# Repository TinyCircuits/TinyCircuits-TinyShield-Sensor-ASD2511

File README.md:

# TinyCircuits TinyShield Sensor Board
# ASD2511 Rev5

The design files are located in the design_files/ folder for the TinyCircuits ASD2511 Rev 5 PCB.  This is a TinyShield board (Square Version, 20mm x 20mm) that has multiple sensor ICs on it and can be built under different configurations based on the sensor needs.  This board includes a 3-axis accelerometer, 3-axis gyroscope, 3-axis compass, 9-axis IMU, barometric pressure, temperature / humidity sensor, & ambient light sensor.  

Format is in Cadsoft Eagle format - Eagle version 6.2 was used for the original design.

For more infomation on this, check out the product pages for sensors at TinyCircuits.com: https://tinycircuits.com/collections/sensors/products/combo-sensor-tinyshield

#License:

Design by TinyCircuits.
All design files are released under the Creative Commons Attribution Share-Alike 3.0 License, see the following link for details: http://creativecommons.org/licenses/by-sa/3.0

All text above must be included in any redistribution or derived design

This project uses designs and concepts developed as part of the Arduino project and the LilyPad project.  The TinyCircuits design files themselves (schematics, PCB and libraries) are not directly derived from these works' design files and have been created new, however the concepts and basic architecture behind the TinyDuino and TinyLily products are derived and we thank the hard work of the organizations below for their contributions to open-source hardware:
  
Original Arduino Uno Design by Team Arduino

LilyPad Arduino Design by Leah Buechley and Sparkfun Electronics

Please support the open-source hardware community

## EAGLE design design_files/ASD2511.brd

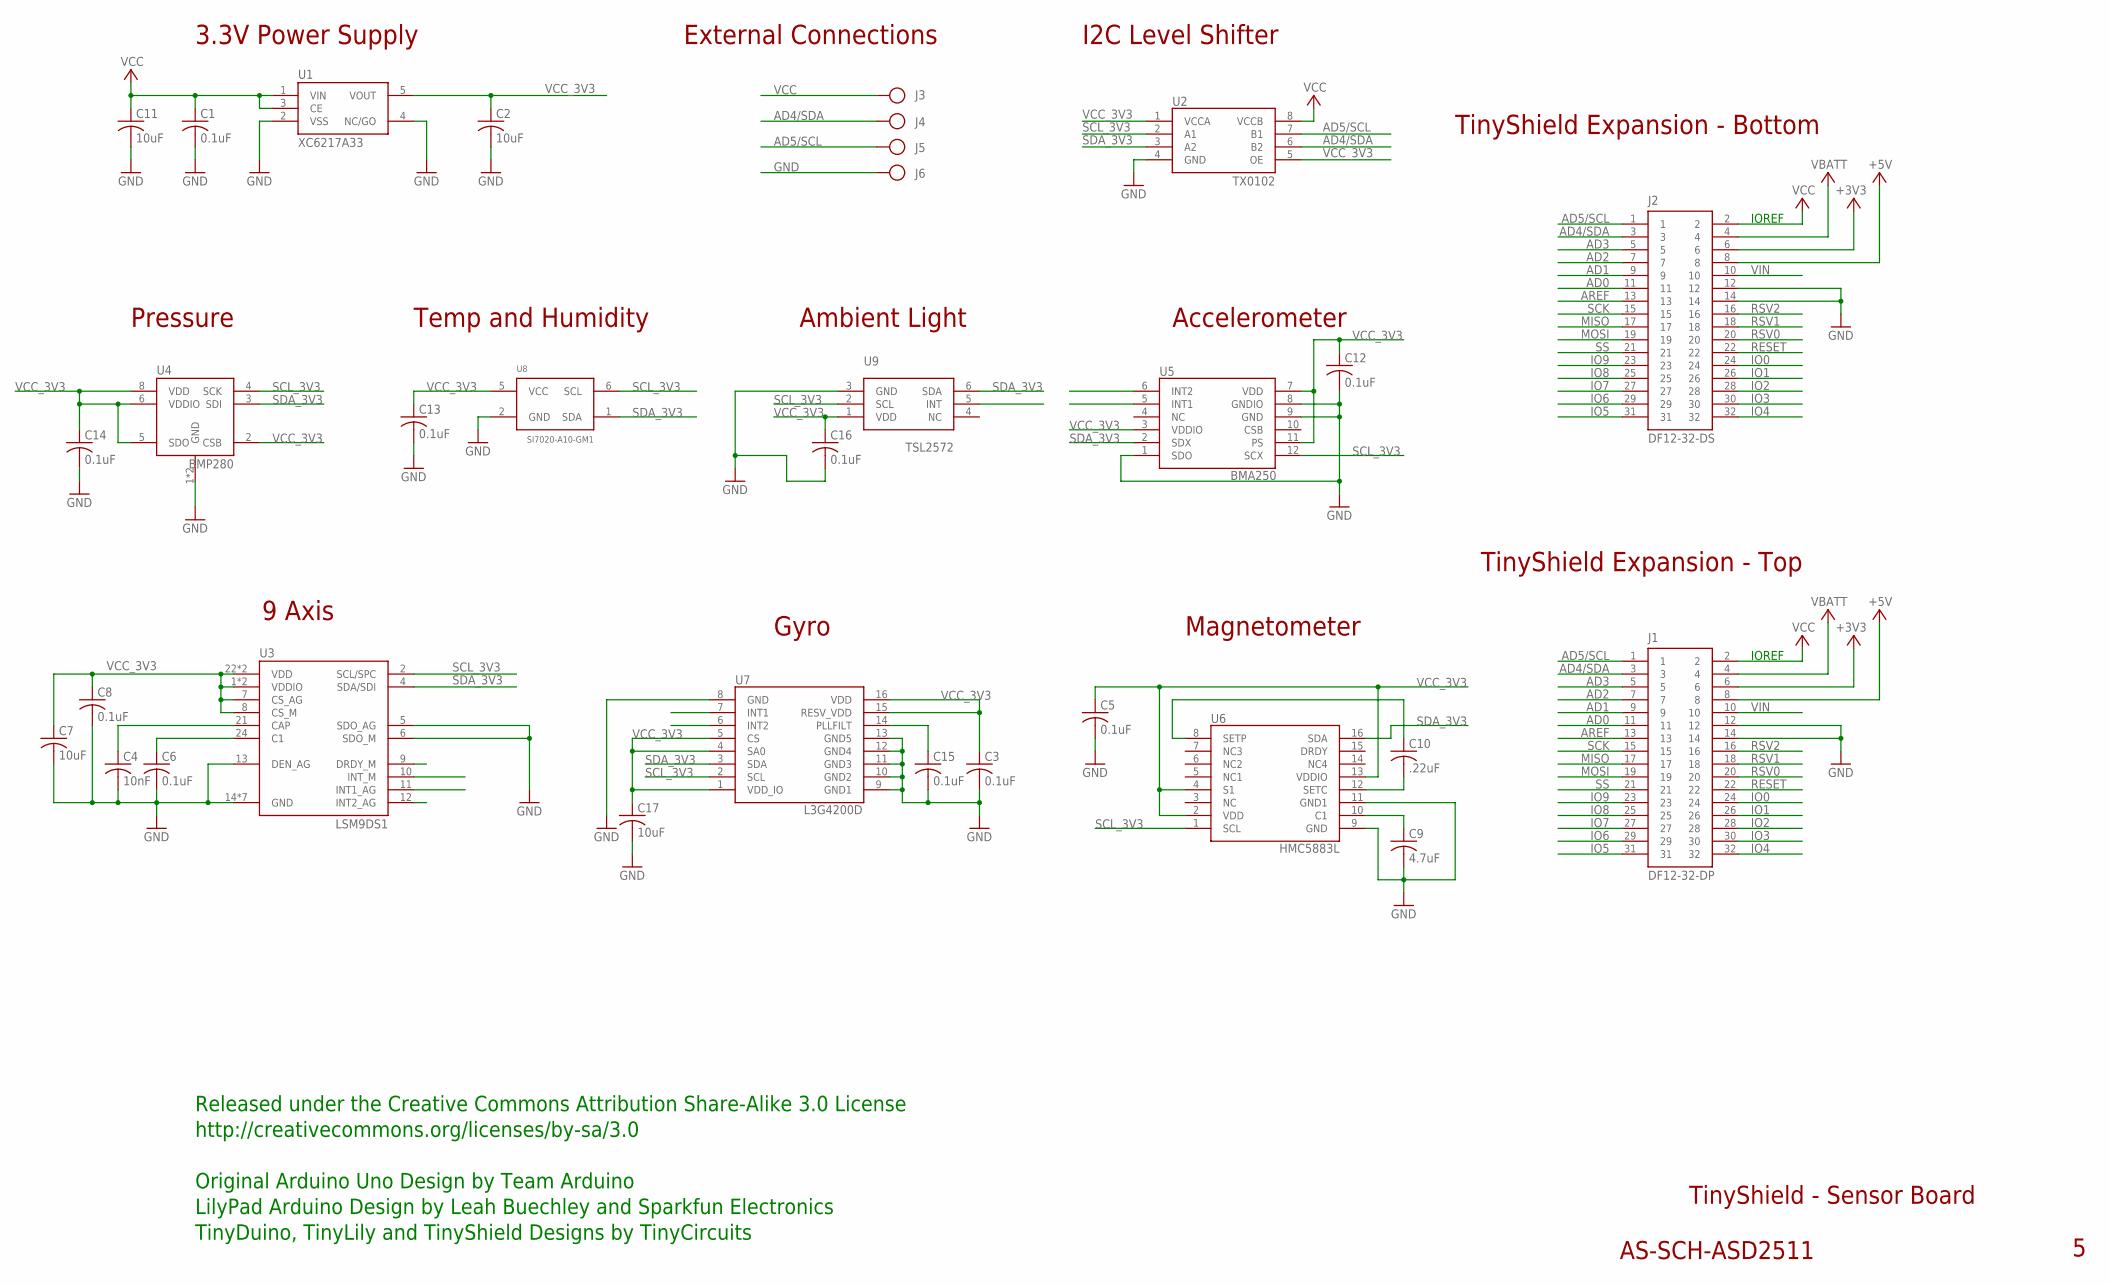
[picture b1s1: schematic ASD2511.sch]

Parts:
C1, C3, C5, C8, C12, C13, C14, C15, C16: 0.1uF; C0402; PARTNO AS-ITM-00008
C2, C7: 10uF; C0603; PARTNO AS-ITM-00002
C4: 10nF; C0402
C6: 0.1uF; C0402
C9: 4.7uF; C0402; PARTNO AS-ITM-00242
C10: .22uF; C0402
C11, C17: 10uF; C0603
J1: DF12-32-DP; PARTNO AS-ITM-00015
J2: DF12-32-DS; PARTNO AS-ITM-00012
J3, J4, J5, J6: PIN_1X.1"1; 1X.1"_2
U1: XC6217A33; SOT-25; PARTNO AS-ITM-00249
U2: TX0102; DQE(R-PX2SON-N8)
U3: LSM9DS1; LGA-24
U4: BMP280
U5: BMA250; 3-AXIS_ACCELEROMETER
U6: HMC5883L
U7: L3G4200D
U8: SI7020-A10-GM1; DFN6
U9: TSL2572

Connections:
+3V3: J1.6, J2.6
+5V: J1.8, J2.8
AD0: J1.11, J2.11
AD1: J1.9, J2.9
AD2: J1.7, J2.7
AD3: J1.5, J2.5
AD4/SDA: J1.3, J2.3, J4.1, U2.6 (B2)
AD5/SCL: J1.1, J2.1, J5.1, U2.7 (B1)
AREF: J1.13, J2.13
GND: C1.2, C2.2, C3.2, C4.2, C5.2, C6.2, C7.2, C8.2, C9.2, C11.2, C12.2, C13.2, C14.2, C15.2, C16.2, C17.2, J1.12, J1.14, J2.12, J2.14, J6.1, U1.2 (VSS), U1.4 (NC/GO), U2.4 (GND), U3.5 (SDO_AG), U3.6 (SDO_M), U3.13 (DEN_AG), U3.14 (GND), U3.15 (GND), U3.16 (GND), U3.17 (GND), U3.18 (GND), U3.19 (GND), U3.20 (GND), U4.1 (GND), U4.7 (GND), U5.1 (SDO), U5.8 (GNDIO), U5.9 (GND), U6.9 (GND), U6.11 (GND1), U7.8 (GND), U7.9 (GND1), U7.10 (GND2), U7.11 (GND3), U7.12 (GND4), U7.13 (GND5), U8.2 (GND), U9.3 (GND)
IO0: J1.24, J2.24
IO1: J1.26, J2.26
IO2: J1.28, J2.28
IO3: J1.30, J2.30
IO4: J1.32, J2.32
IO5: J1.31, J2.31
IO6: J1.29, J2.29
IO7: J1.27, J2.27
IO8: J1.25, J2.25
IO9: J1.23, J2.23
MISO: J1.17, J2.17
MOSI: J1.19, J2.19
unnamed: C4.1, U3.21 (CAP)
unnamed: C15.1, U7.14 (PLLFILT)
unnamed: C9.1, U6.10 (C1)
unnamed: C6.1, U3.24 (C1)
unnamed: C10.2, U6.12 (SETC)
unnamed: C10.1, U6.8 (SETP)
RESET: J1.22, J2.22
RSV0: J1.20, J2.20
RSV1: J1.18, J2.18
RSV2: J1.16, J2.16
SCK: J1.15, J2.15
SCL_3V3: U2.2 (A1), U3.2 (SCL/SPC), U4.4 (SCK), U5.12 (SCX), U6.1 (SCL), U7.2 (SCL), U8.6 (SCL), U9.2 (SCL)
SDA_3V3: U2.3 (A2), U3.4 (SDA/SDI), U4.3 (SDI), U5.2 (SDX), U6.16 (SDA), U7.3 (SDA), U8.1 (SDA), U9.6 (SDA)
SS: J1.21, J2.21
VBATT: J1.4, J2.4
VCC: C1.1, C11.1, J1.2, J2.2, J3.1, U1.1 (VIN), U1.3 (CE), U2.8 (VCCB)
VCC_3V3: C2.1, C3.1, C5.1, C7.1, C8.1, C12.1, C13.1, C14.1, C16.1, C17.1, U1.5 (VOUT), U2.1 (VCCA), U2.5 (OE), U3.1 (VDDIO), U3.3 (VDDIO), U3.7 (CS_AG), U3.8 (CS_M), U3.22 (VDD), U3.23 (VDD), U4.2 (CSB), U4.5 (SDO), U4.6 (VDDIO), U4.8 (VDD), U5.3 (VDDIO), U5.7 (VDD), U5.11 (PS), U6.2 (VDD), U6.4 (S1), U6.13 (VDDIO), U7.1 (VDD_IO), U7.4 (SA0), U7.5 (CS), U7.15 (RESV_VDD), U7.16 (VDD), U8.5 (VCC), U9.1 (VDD)
VIN: J1.10, J2.10

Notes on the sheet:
TinyShield Expansion - Bottom
TinyShield - Sensor Board
AS-SCH-ASD2511
TinyShield Expansion - Top
IOREF
Released under the Creative Commons Attribution Share-Alike 3.0 License
http://creativecommons.org/licenses/by-sa/3.0
LilyPad Arduino Design by Leah Buechley and Sparkfun Electronics
TinyDuino, TinyLily and TinyShield Designs by TinyCircuits
Original Arduino Uno Design by Team Arduino
External Connections
3.3V Power Supply
I2C Level Shifter
9 Axis
Pressure
Temp and Humidity
Ambient Light
Accelerometer
Gyro
Magnetometer

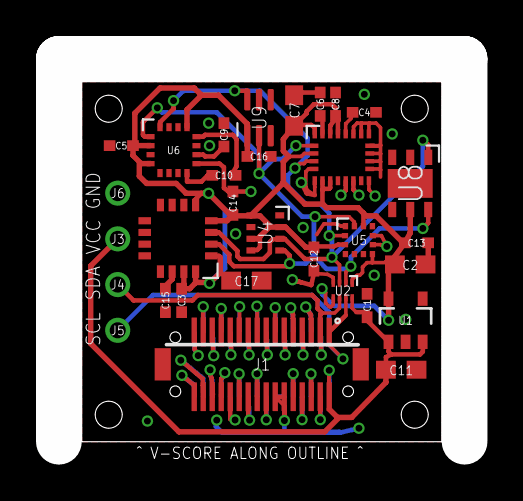
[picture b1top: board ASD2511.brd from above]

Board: 2 copper layers, 20.0 x 20.0 mm, 33 parts (1 on the bottom side), 40 nets.

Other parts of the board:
U$1: DOCFIELD-TINYCIRCUITS-PCB

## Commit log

2015-10-19 :octocat: Added .gitattributes & .gitignore files
2017-03-22 Added sample sketches
2019-01-02 update format
2019-01-02 update datasheets
2019-01-02 filename change
2019-01-02 update library and datasheet
2019-01-02 add library
2019-01-07 updated comments
2019-01-10 updated libraries
2019-01-11 added images
2019-01-11 added serial monitor images
2019-01-11 added .zip files
2019-01-11 added .zip for libraries
2019-01-11 fixed pressure sensor image
2019-01-11 updated images
2019-02-25 add tutorial images
2019-03-15 Add accelerometer stuff
2019-03-18 add accel pictures
2019-03-25 add images
2019-03-26 Add compass example
2019-05-17 update zip files
2019-05-22 updated examples and libraries
2019-05-23 oops, wrong board!
2019-05-23 tools
2020-01-10 add combination example of combo sensors
2020-01-17 guess I didn't push this
2020-02-11 image update
2020-04-29 Negative pressure fix by Willem - thanks!
2020-07-28 Add CAD data
2020-08-14 Update CAD drawing
2021-05-24 update si7021 code
